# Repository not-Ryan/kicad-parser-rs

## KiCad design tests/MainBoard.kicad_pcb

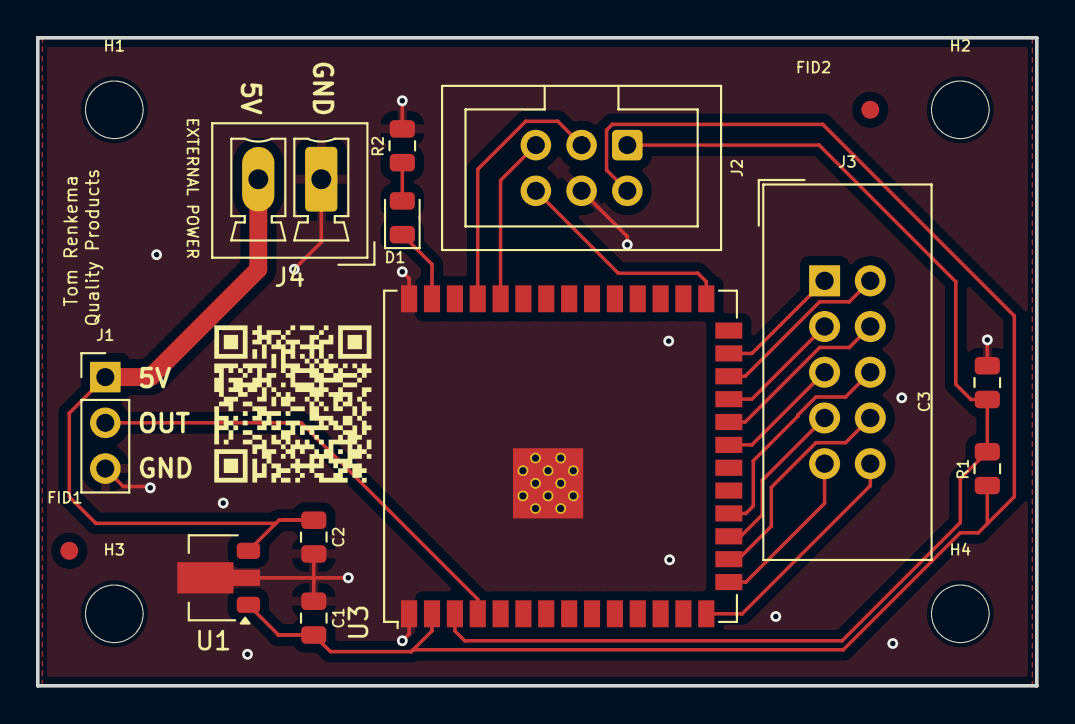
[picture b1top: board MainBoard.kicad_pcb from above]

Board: 2 copper layers, 55.5 x 36.0 mm, 18 parts (0 on the bottom side), 20 nets.

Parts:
C1, C2, C3: 1u; C_0805
D1: LED0805; LED_0805
FID1, FID2: Fiducial; Fiducial_1mm_Mask2mm
H1, H2, H3, H4: MountingHole3.2mm; MountingHole_3.2mm_M3_ISO14580
J1: CON-H1x3V
J2: CON-H2x3V; CON-BH2x03V
J3: CON-BH2x05V
J4: CON-MCV2V-3.50mm; CON_MCV2V-3.50mm
R1: 10k; R_0805
R2: 680; R_0805
U1: LDI1117_SOT89; SOT-89-3
U3: ESP32-S3-WROOM-1U

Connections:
+3V3: C1.2, J2.2, R1.1, U1.1 (OUT), U3.2 (3V3)
+5V: C2.1, J1.1, J4.2, U1.3 (IN)
GND: C1.1, C2.2, C3.1, J1.3, J2.4, J4.1, R2.2, U1.2 (GND), U3.1 (GND), U3.40 (GND), U3.41 (GND)
unnamed: D1.2 (A), R2.1
unnamed: D1.1 (K), U3.39 (IO01)
unnamed: J1.2, U3.4 (IO04)
unnamed: C3.2, J2.1, R1.2, U3.3 (EN)
unnamed: J2.3, U3.37 (TXD0)
unnamed: J2.5, U3.36 (RXD0)
unnamed: J2.6, U3.27 (BOOT/IO00)
unnamed: J3.1, U3.25 (IO48)
unnamed: J3.2, U3.24 (IO47)
unnamed: J3.3, U3.23 (IO21)
unnamed: J3.4, U3.22 (IO14)
unnamed: J3.5, U3.21 (IO13)
unnamed: J3.6, U3.18 (IO10)
unnamed: J3.7, U3.17 (IO09)
unnamed: J3.8, U3.16 (IO46/BOOT/ROM)
unnamed: J3.9, U3.15 (IO03/nJTAG)
unnamed: J3.10, U3.14 (IO20/USB-JTAG)

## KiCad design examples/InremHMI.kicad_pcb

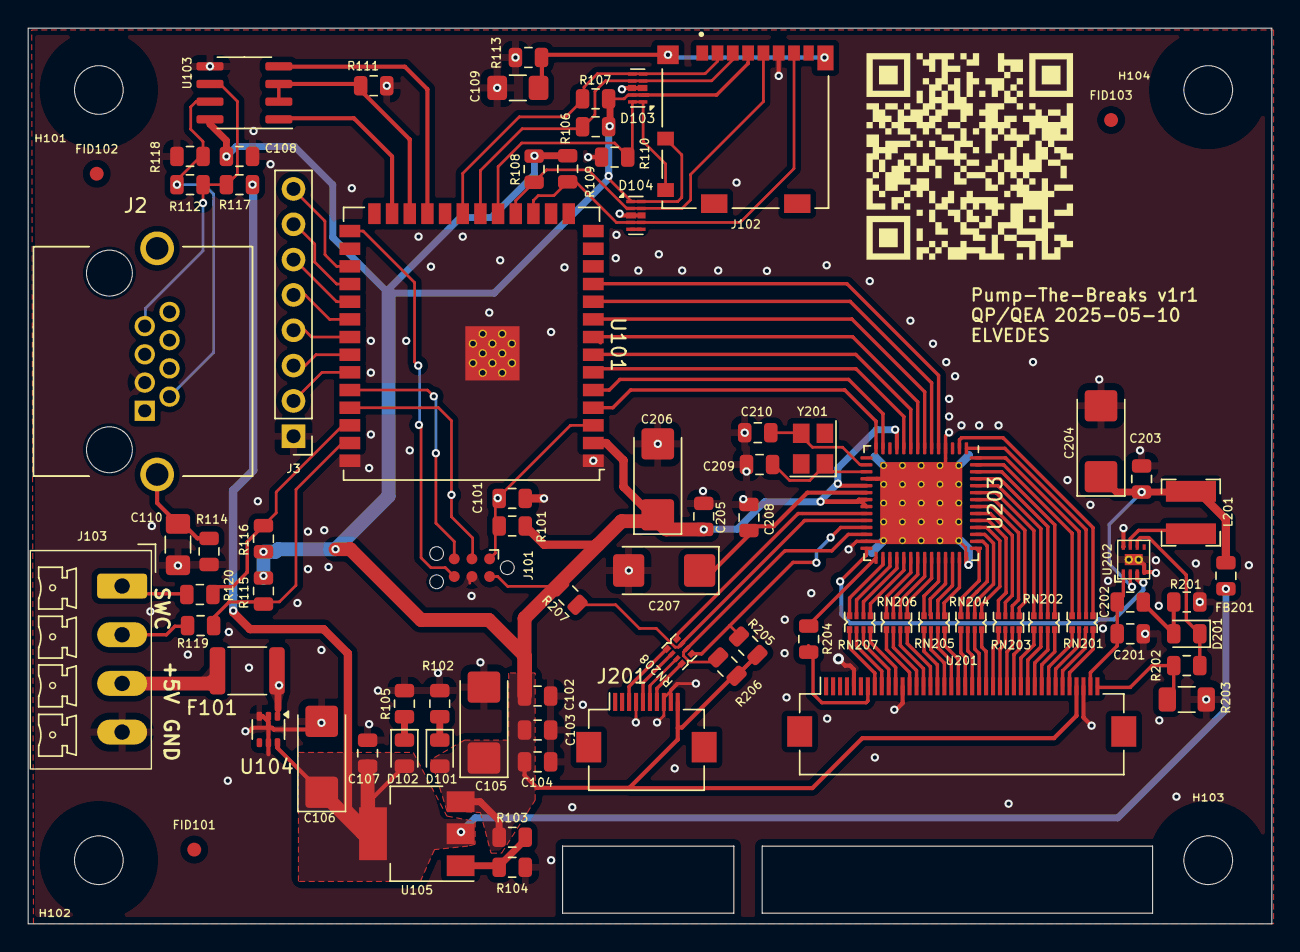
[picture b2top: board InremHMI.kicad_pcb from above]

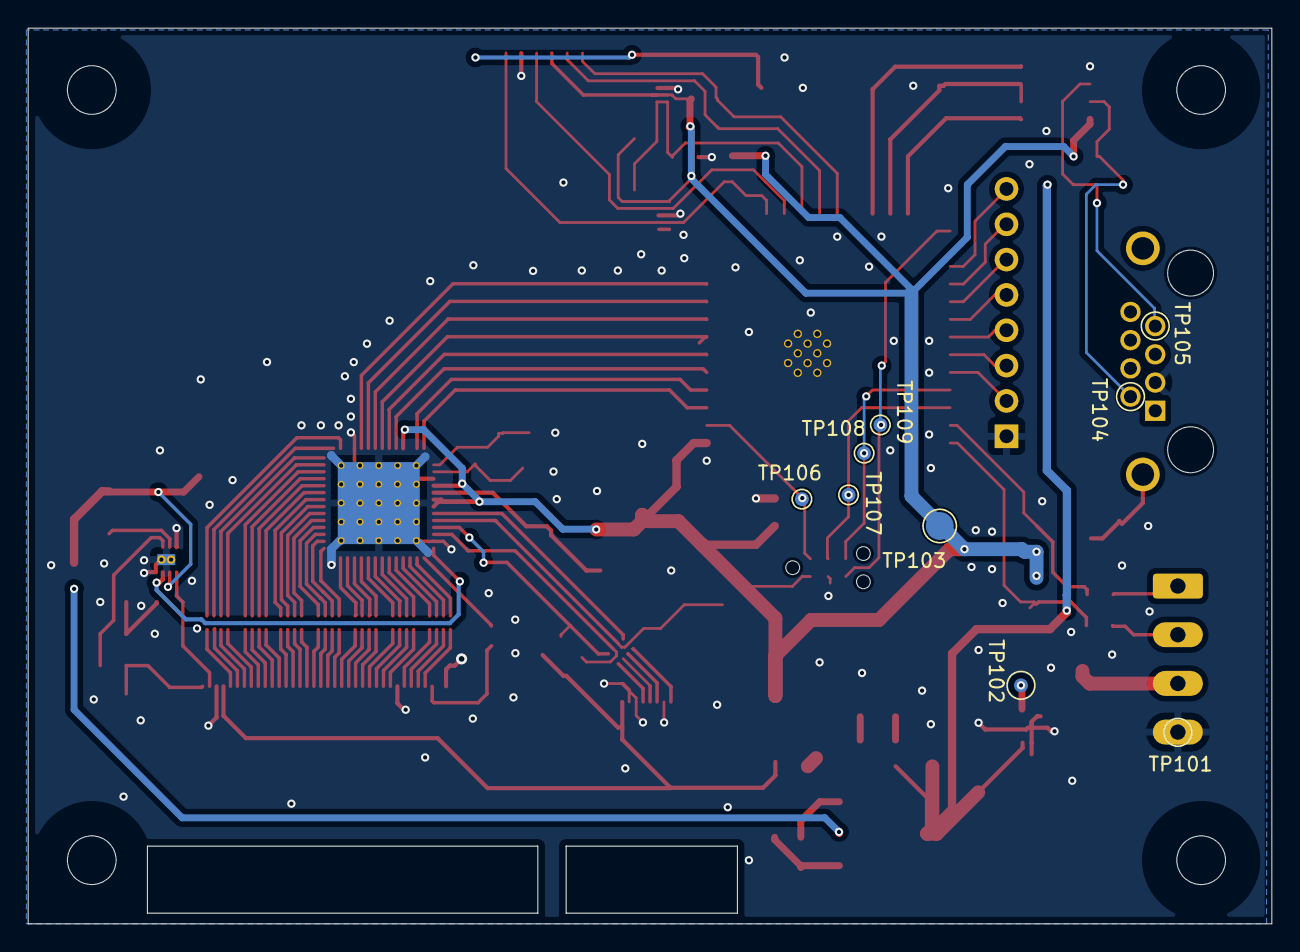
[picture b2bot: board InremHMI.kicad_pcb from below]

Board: 2 copper layers, 89.4 x 64.4 mm, 93 parts (9 on the bottom side), 120 nets.

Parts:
C101, C104: 1u; C_0805
C102, C107, C108, C203, C205: 100n; C_0805
C103, C208: 220n; C_0805
C105, C106: 3u3; Case-C
C109, C110: 1n/2kV; C_1206
C201: 220n,25V; C_0805
C202: 2n2,25V; C_0805
C204, C206, C207: 10u; Case-C
C209, C210: 15p; C_0805
D101: BLUE; LED_0805
D102: RED; LED_0805
D103, D104: TVS-4x3V3-DFN2510-10; Diodes_UDFN-10_1.0x2.5mm_P0.5mm
D201: 1N4148; D_0805
F101: 0.5A; Fuse_1812_4532Metric
FB201: 220R; L_0805
FID101, FID102, FID103: Fiducial; Fiducial_1mm_Mask2mm
H101, H102, H103, H104: M3pad; MountingHole_3.5mm
J2: CON-RJ45S; RJHSE5380
J3: CON-H1x8V
J101: Prog; TC2030-IDC-NL
J102: Molex_uSDCARD_104031-0811; MOLEX_104031-0811
J103: PWR/SW; CON_MCV4H-3.50mm
J201: FH12-10S-0.5SH; Hirose_FH12-10S-0.5SH_1x10-1MP_P0.50mm_Horizontal
L201: 22uH; L_Bourns-SRN4018
R101, R106, R107, R108, R109, R110, R111, R115, R116, R119, R120, R201: 10K; R_0805
R102, R103: 220R; R_0805
R104: 360R; R_0805
R105: 1K; R_0805
R112, R113, R114: 120R; R_0805
R117, R118: 680R; R_0805
R202: 4K7; R_0805
R203: 1R6; R_1206
R204: 33R; R_0805
R205, R206, R207: 2K2; R_0805
RN201, RN202, RN203, RN204, RN205, RN206, RN207, RN208: 33R; CAY10
TP101: GND; TestPoint_VirtualPad_D1.0mm
TP102: 5V; TestPoint_VirtualPad_D1.0mm
TP103: 3V3; TestPoint_Pad_D2.0mm
TP104: RS485_{B}; TestPoint_VirtualPad_D1.0mm
TP105: RS485_{A}; TestPoint_VirtualPad_D1.0mm
TP106: ESP_{EN}; TestPoint_Pad_D1.0mm
TP107: ESP_{TXD0}; TestPoint_Pad_D1.0mm
TP108: ESP_{RX0}; TestPoint_Pad_D1.0mm
TP109: ESP_{BOOT}; TestPoint_Pad_D1.0mm
U101: ESP32-S3-WROOM-1U
U103: THVD1420; SO-8
U104: LM66100DCK; SOT-363_SC-70-6
U105: LM317_SOT223; SOT-223-3_T2
U201: TST043015CMHX; FH12A-40S-0.5SH_1x40-1MP_P0.50mm_Horizontal
U202: MIC2289-24; MLF-8-1EP_2x2mm_P0.5mm_EP0.8x1.3mm_ThermalVias
U203: FT813Q-T; QFN-56-1EP_8x8mm_P0.5mm_EP5.9x5.9mm_ThermalVias
Y201: 12MHz; Crystal_3225-4

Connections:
+3.3V: C102.1, C103.1, C104.1, C105.1, C108.2, C205.2, C206.1, D101.2 (A), D103.2 (K), D103.9 (K), D104.1 (K), D104.10 (K), J101.2, J102.4 (VDD), J102.9 (DET_A), J201.10, R101.1, R103.1, R106.2, R107.2, R108.2, R109.2, R115.2, R116.2, R205.2, R206.2, R207.2, TP103.1, U101.2 (3V3), U103.8 (VCC), U105.3 (VI), U201.4 (VDD), U203.11 (VCCIO1), U203.19 (Vcc), U203.21 (VCC), U203.22 (VCCIO2)
+5V: C106.1, C107.2, D102.2 (A), FB201.1, R117.2, U104.6 (VOUT), U105.2 (VO)
/BT8xLCD/INT_N: U101.5 (IO05), U203.13 (INT_N)
/BT8xLCD/PD_N: U101.4 (IO04), U203.14 (PD_N)
/BT8xLCD/SPI_CS: U101.8 (IO15), U203.8 (CS_N)
/BT8xLCD/SPI_D0: U101.9 (IO16), U203.7 (MOSI/IO0)
/BT8xLCD/SPI_D1: U101.10 (IO17), U203.6 (MISO/IO1)
/BT8xLCD/SPI_D2: U101.7 (IO07), U203.9 (GPIO0/IO2)
/BT8xLCD/SPI_D3: U101.6 (IO06), U203.10 (GPIO1/IO3)
/BT8xLCD/SPI_SCK: U101.11 (IO18), U203.5 (SCK)
DISP_BL: U202.3 (EN), U203.28 (BACKLIGHT)
DISP_CLK: RN207.4 (R4.1), U201.30 (CLK)
DISP_DEN: R204.2, U201.34 (DATA_EN)
DISP_EN: RN207.3 (R3.1), U201.31 (DISP_EN)
DISP_HSYNC: RN207.2 (R2.1), U201.32 (Hsync)
DISP_VSYNC: RN207.1 (R1.1), U201.33 (Vsync)
GND: C101.1, C102.2, C103.2, C104.2, C105.2, C106.2, C107.1, C108.1, C109.1, C110.1, C201.2, C203.2, C204.2, C205.1, C206.2, C207.2, C208.1, C209.2, C210.2, D103.3 (A), D103.8 (K), D104.3 (A), D104.8 (K), J2.3, J3.1, J101.4, J102.6 (VSS), J103.4, J201.4, J201.8, J201.9, R102.2, R104.2, R105.2, R110.2, R111.2, R113.1, R114.1, R118.1, R201.2, R203.2, TP101.1, U101.1 (GND), U101.40 (GND), U101.41 (GND), U103.5 (GND), U104.2 (GND), U104.3 (~CE), U104.5 (ST), U201.3 (GND), U201.29 (GND), U201.36 (GND), U202.4 (AGND), U202.8 (PGND), U202.9 (EP_GND), U203.4 (GND), U203.18 (GND), U203.27 (GND), U203.42 (GND), U203.57 (EPAD)
unnamed: C110.2, J2.SH, R114.2
unnamed: D101.1 (K), R102.1
unnamed: D102.1 (K), R105.1
unnamed: D104.5 (K), D104.6 (K)
unnamed: C202.2, D201.2 (A), R201.1
unnamed: D201.1 (K), R202.1, U202.6 (FB)
unnamed: J3.2, U101.35 (MTMS/IO42)
unnamed: J3.3, U101.34 (MTCK/IO41)
unnamed: J3.4, U101.33 (MTDI/IO40)
unnamed: J3.5, U101.32 (MTDO/IO39)
unnamed: J3.6, U101.31 (IO38)
unnamed: J3.7, U101.30 (IO37)
unnamed: J3.8, U101.29 (IO36)
unnamed: C101.2, J101.1, R101.2, TP106.1, U101.3 (EN)
unnamed: J101.3, TP107.1, U101.37 (TXD0)
unnamed: J101.5, TP108.1, U101.36 (RXD0)
unnamed: J101.6, TP109.1, U101.27 (BOOT/IO00)
unnamed: D103.5 (K), D103.6 (K), J102.2 (CD/DAT3), R107.1, U101.21 (IO13)
unnamed: D104.2 (K), D104.9 (K), J102.5 (CLK), R108.1, U101.18 (IO10)
unnamed: D103.4 (K), D103.7 (K), J102.3 (CMD), R106.1, U101.20 (IO12)
unnamed: D104.4 (K), D104.7 (K), J102.7 (DAT0), R109.1, U101.17 (IO09)
unnamed: D103.1 (K), D103.10 (K), J102.10 (DET_B), R110.1, U101.19 (IO11)
unnamed: C109.2, J102.G1 (Shield), R113.2
unnamed: J103.1, R120.2
unnamed: J103.2, R119.2
unnamed: F101.2, J103.3
unnamed: J201.3, RN208.5 (R4.2)
unnamed: J201.5, RN208.6 (R3.2)
unnamed: J201.6, RN208.7 (R2.2)
unnamed: J201.7, RN208.8 (R1.2)
unnamed: RN201.1 (R1.1), U201.8 (R3)
unnamed: RN201.8 (R1.2), U203.55 (R3)
unnamed: RN201.2 (R2.1), U201.7 (R2)
unnamed: RN201.7 (R2.2), U203.56 (R2)
unnamed: RN201.3 (R3.1), U201.6 (R1)
unnamed: RN201.6 (R3.2), U203.1 (R1)
unnamed: RN201.4 (R4.1), U201.5 (R0)
unnamed: RN201.5 (R4.2), U203.2 (R0)
unnamed: RN202.1 (R1.1), U201.12 (R7)
unnamed: RN202.8 (R1.2), U203.51 (R7)
unnamed: RN202.2 (R2.1), U201.11 (R6)
unnamed: RN202.7 (R2.2), U203.52 (R6)
unnamed: RN202.3 (R3.1), U201.10 (R5)
unnamed: RN202.6 (R3.2), U203.53 (R5)
unnamed: RN202.4 (R4.1), U201.9 (R4)
unnamed: RN202.5 (R4.2), U203.54 (R4)
unnamed: RN203.1 (R1.1), U201.16 (G3)
unnamed: RN203.8 (R1.2), U203.47 (G3)
unnamed: RN203.2 (R2.1), U201.15 (G2)
unnamed: RN203.7 (R2.2), U203.48 (G2)
unnamed: RN203.3 (R3.1), U201.14 (G1)
unnamed: RN203.6 (R3.2), U203.49 (G1)
unnamed: RN203.4 (R4.1), U201.13 (G0)
unnamed: RN203.5 (R4.2), U203.50 (G0)
unnamed: RN204.1 (R1.1), U201.20 (G7)
unnamed: RN204.8 (R1.2), U203.43 (G7)
unnamed: RN204.2 (R2.1), U201.19 (G6)
unnamed: RN204.7 (R2.2), U203.44 (G6)
unnamed: RN204.3 (R3.1), U201.18 (G5)
unnamed: RN204.6 (R3.2), U203.45 (G5)
unnamed: RN204.4 (R4.1), U201.17 (G4)
unnamed: RN204.5 (R4.2), U203.46 (G4)
unnamed: RN205.1 (R1.1), U201.24 (B3)
unnamed: RN205.8 (R1.2), U203.38 (B3)
unnamed: RN205.2 (R2.1), U201.23 (B2)
unnamed: RN205.7 (R2.2), U203.39 (B2)
unnamed: RN205.3 (R3.1), U201.22 (B1)
unnamed: RN205.6 (R3.2), U203.40 (B1)
unnamed: RN205.4 (R4.1), U201.21 (B0)
unnamed: RN205.5 (R4.2), U203.41 (B0)
unnamed: RN206.1 (R1.1), U201.28 (B7)
unnamed: RN206.8 (R1.2), U203.34 (B7)
unnamed: RN206.2 (R2.1), U201.27 (B6)
unnamed: RN206.7 (R2.2), U203.35 (B6)
unnamed: RN206.3 (R3.1), U201.26 (B5)
unnamed: RN206.6 (R3.2), U203.36 (B5)
unnamed: RN206.4 (R4.1), U201.25 (B4)
unnamed: RN206.5 (R4.2), U203.37 (B4)
unnamed: RN207.8 (R1.2), U203.30 (VSYNC)
unnamed: RN207.7 (R2.2), U203.31 (HSYNC)
unnamed: RN207.6 (R3.2), U203.32 (DISP)
unnamed: RN207.5 (R4.2), U203.33 (PCLK)
unnamed: R205.1, RN208.1 (R1.1), U203.25 (CTP_SCL)
unnamed: R206.1, RN208.2 (R2.1), U203.26 (CTP_SDA)
unnamed: R207.1, RN208.3 (R3.1), U203.24 (CTP_INT_N)
unnamed: RN208.4 (R4.1), U203.23 (CTP_RST_N)
unnamed: R115.1, R119.1, U101.39 (IO01)
unnamed: R116.1, R120.1, U101.38 (IO02)
unnamed: U101.23 (IO21), U103.4 (DI)
unnamed: R111.1, U101.24 (IO47), U103.2 (~RE), U103.3 (DE)
unnamed: U101.25 (IO48), U103.1 (RO)
unnamed: J2.7, R112.2, R117.1, TP105.1, U103.6 (A)
unnamed: J2.2, R112.1, R118.2, TP104.1, U103.7 (B)
unnamed: F101.1, TP102.1, U104.1 (VIN)
unnamed: R103.2, R104.1, U105.1 (ADJ)
unnamed: C201.1, C202.1, U201.2 (Vled+), U202.1 (OUT)
unnamed: R202.2, R203.1, U201.1 (Vled-)
unnamed: L201.2, U202.7 (SW)
unnamed: C203.1, C204.1, FB201.2, L201.1, U202.2 (VIN)
unnamed: R204.1, U203.29 (DE)
unnamed: C207.1, C208.2, U203.20 (VOUT1V2)
unnamed: C210.1, U203.16 (X1/CLK), Y201.3
unnamed: C209.1, U203.17 (X2), Y201.1

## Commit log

2025-07-09 sexpr parser
2025-07-10 before listing
2025-07-10 this is something with tryfrom but with context... Ples stup
2025-07-10 further
2025-07-10 feat: Wow we can now get anything
2025-07-10 also do not populate
2025-07-10 v0.0.1
2025-07-11 fix: Footprint description not getting parsed
2025-07-11 v0.0.2
2025-08-12 optional serde feature
2025-08-28 Rename to kicad-parser
2025-08-28 cargo.lock update
2025-08-28 add license
2025-08-28 Add svg rendering example
2025-08-28 Version bump
2025-09-10 Allow unspecified
2025-11-17 Add bbox center fn & v0.0.5
2025-11-17 v0.0.5
2025-11-18 Try fix offset
2025-11-21 Fix positionals
2025-11-21 v0.0.6
2025-11-21 Support arc graphic
2025-11-21 0.0.7
2026-01-07 Fix angle
2026-03-18 Fix knockout layer attributes & Fix tests
2026-03-18 LFS?
2026-03-18 v0.0.9
2026-05-15 Add pad & polygon bounding boxes
2026-05-15 More attempted fixes
2026-05-15 Fix bottom rendering & positioning
2026-05-15 Fix mirror on F.Cu
